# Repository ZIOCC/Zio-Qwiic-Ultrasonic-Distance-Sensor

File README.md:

# Zio Qwiic Ultrasonic Distance Sensor (HC-SR04)

> This product can be available for purchase [here](https://www.smart-prototyping.com/Zio-Ultrasonic-Distance-Sensor.html).

#### Description

This is a [Qwiic](https://www.smart-prototyping.com/Qwiic.html) I2C version of ultrasonic sensor in our Qwiic family. TOF sensor is great, precise and fast, but this Ultrasonic sensor can provide wider detecting angle than TOF sensor and longer distance (3-400cm).

With this module we used a STM8 MCU as gateway to deal with sensor’s digital data in MCU, and send it out via I2C. So you don’t need to care about how it works inside the STM8, just trade it as an I2C device. In case you are interesting, you can check out the STM8 code at the bottom of the links.

We also break the serial pins just like the normal HC-SR04 module. The pins are not pre-soldered. We use an MCU (ATTINY85-20SU) as gateway to turn it into an I2C device.

For additional information on how the Ultrasonic sensor works, you can check out this [page](http://arduinoinfo.mywikis.net/wiki/UltraSonicDistance)!

Note: Try to avoid touching the pins and pads on the backside, the sensor measurement is based on analog single, touching these pins and pads will make the result unstable. 

#### Specification

* Operating Voltage: 3.3V
* Detecting Angle: 15 degree
* Sensor range: 2cm to 400cm
* Accuracy: 3mm
* MCU on board: STM8L051
* I2C Address: 0x00
* Dimension: 21.5x 45.5mm
* Weight: 9.2g

#### Links

* [Eagle File](https://github.com/ZIOCC/Zio-Qwiic-Ultrasonic-Distance-Sensor/)
* [Example Code](https://github.com/ZIOCC/Zio-Qwiic-Ultrasonic-Distance-Sensor/tree/master/Arduino)

###### About Zio
> Zio is a new line of open sourced, compact, and grid layout boards, fully integrated for Arduino and Qwiic ecosystem. Designed ideally for wearables, robotics, small-space limitations or other on the go projects. Check out other awesome Zio products [here](https://www.smart-prototyping.com/Zio).

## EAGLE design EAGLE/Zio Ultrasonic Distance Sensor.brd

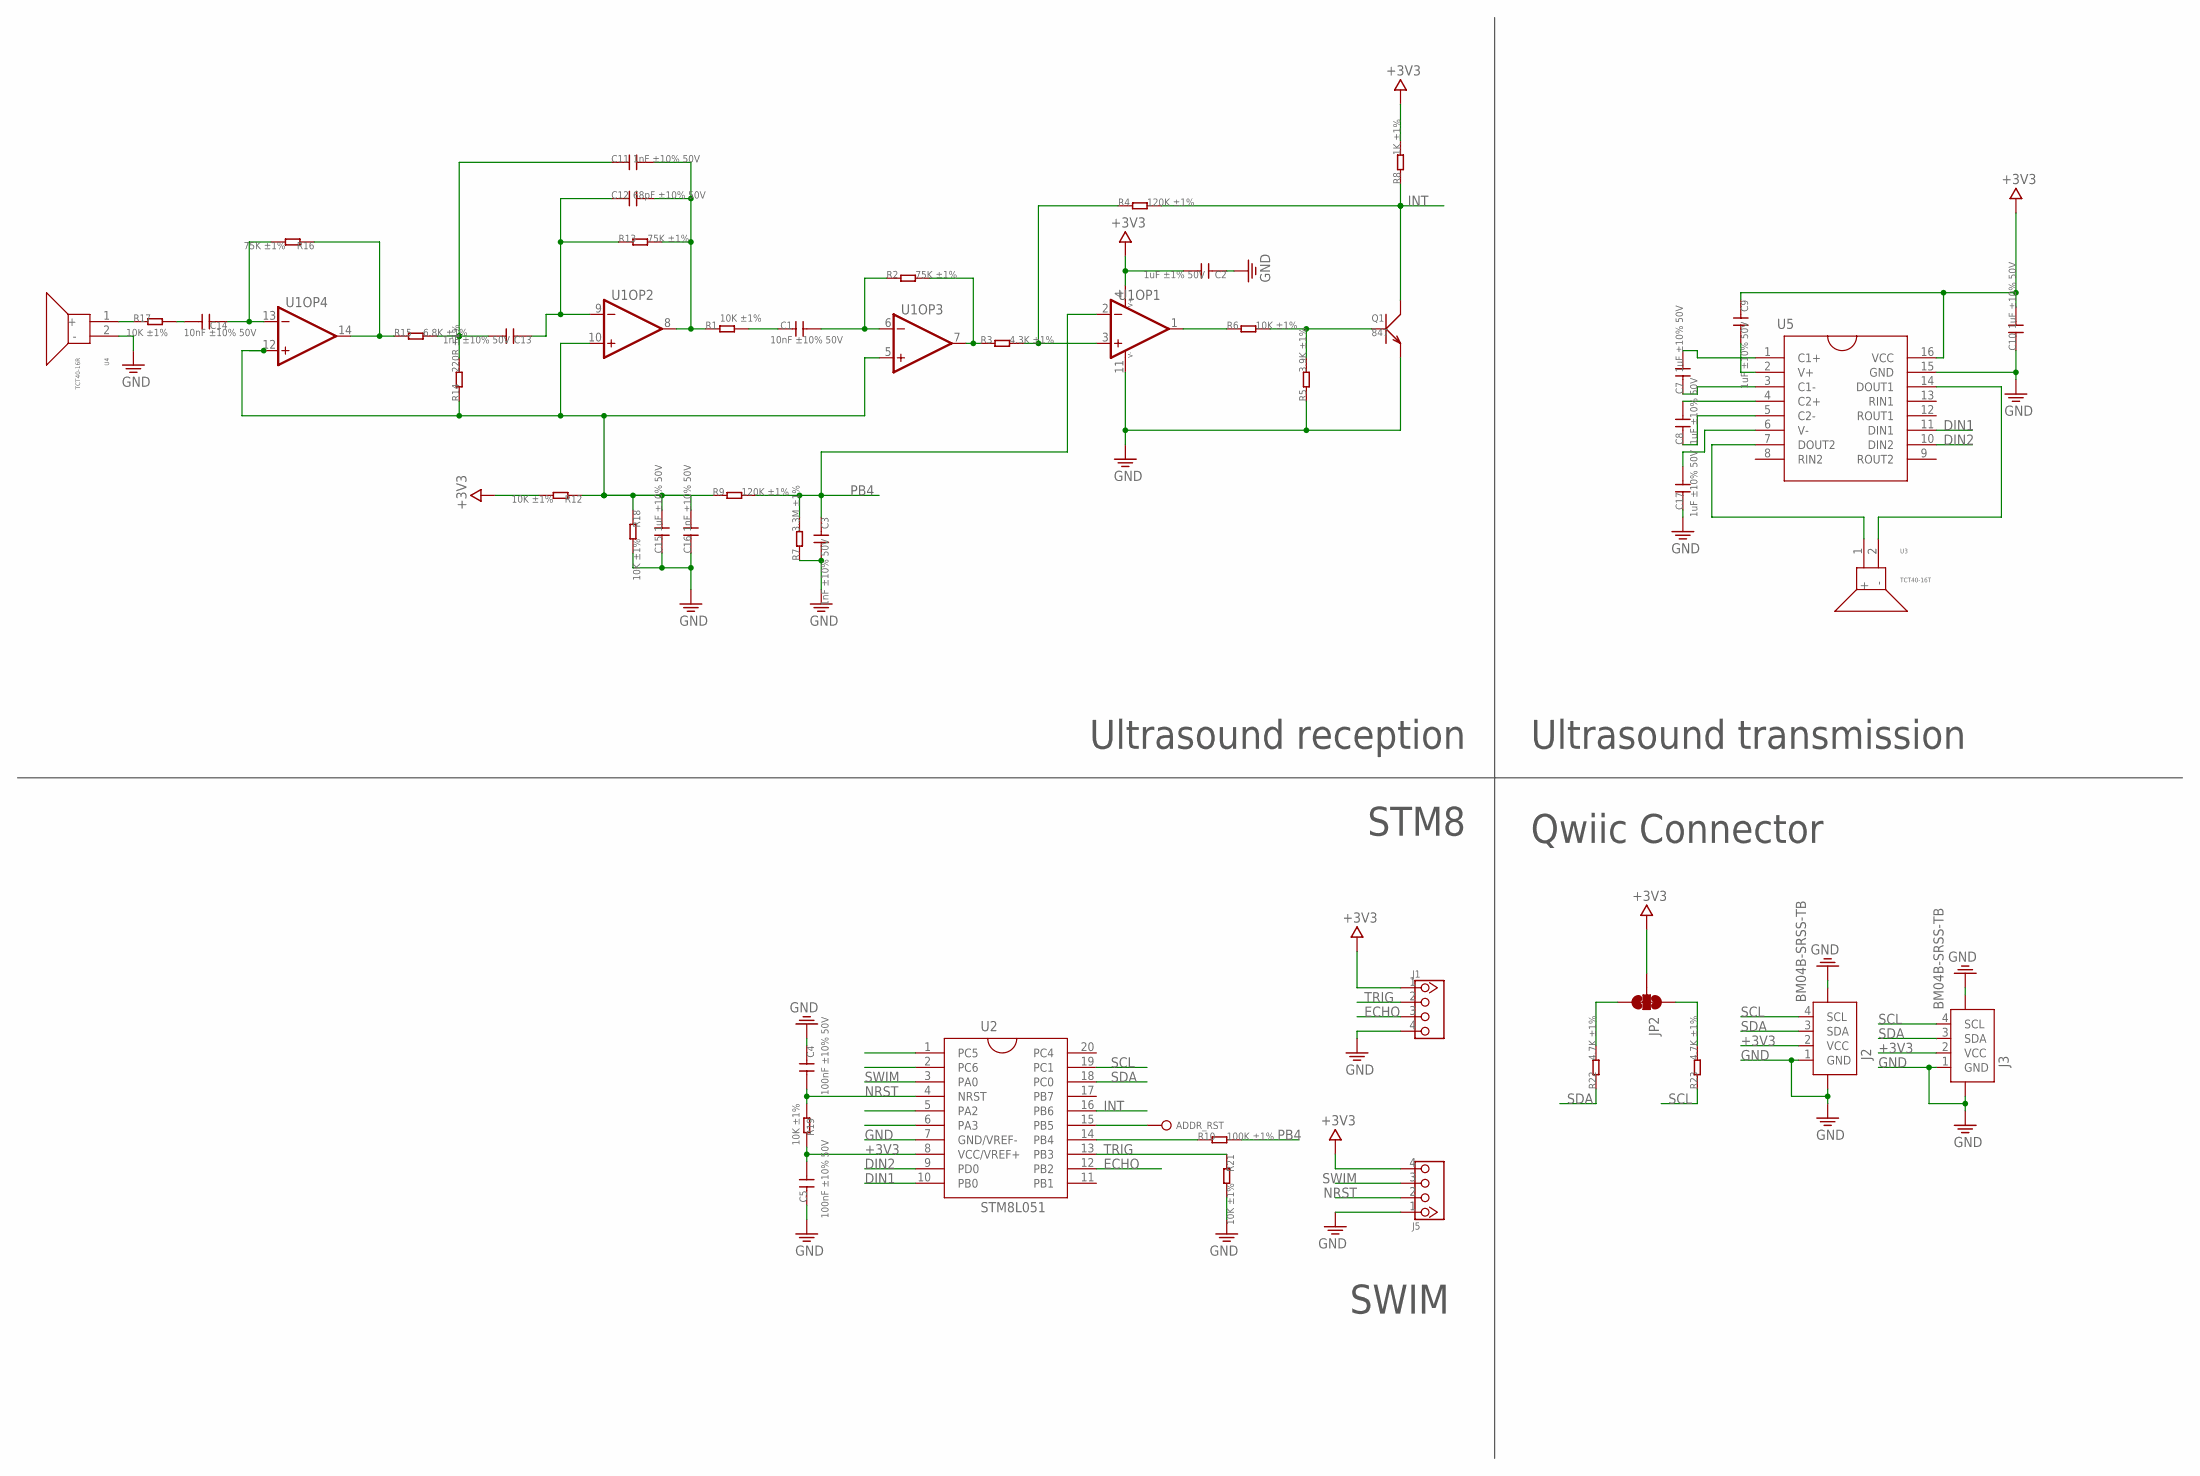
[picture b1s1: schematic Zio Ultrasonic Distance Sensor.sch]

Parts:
ADDR_RST: TEST_POINT35MIL; 1P-35MIL
C1, C14: 10nF ±10% 50V; 0603
C2: 1uF ±1% 50V; 0603
C3, C11, C13, C16: 1nF ±10% 50V; 0603
C4, C5: 100nF ±10% 50V; 0603
C7, C8, C9, C10, C15, C17: 1uF ±10% 50V; 0603
C12: 68pF ±10% 50V; 0603
J1: HEADER-4P-60/35MIL; 4P-65/35MIL
J2, J3: BM04B-SRSS-TB; JST-SH-4P-90
J5: HEADER-4P-TEST_3.08_4P; TEST_3.08_4P
JP2: SMT-JUMPER_3_2-NC_TRACE
Q1: 847; SOT23
R1, R6, R12, R17, R18, R19, R21: 10K ±1%; 0603
R2, R13, R16: 75K ±1%; 0603
R3: 4.3K ±1%; 0603
R4, R9: 120K ±1%; 0603
R5: 3.9K ±1%; 0603
R7: 3.3M ±1%; 0603
R8: 1K ±1%; 0603
R10: 100K ±1%; 0603
R14: 220R ±1%; 0603
R15: 6.8K ±1%; 0603
R22, R23: 4.7K ±1%; 0603
U1: LMV324; SO014
U2: STM8L051; TSSOP20
U3: TCT40-16T; TCT40-16T/R
U4: TCT40-16R; TCT40-16T/R
U5: UT3232G-S16-RSOIC-16; SOIC16

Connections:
+3V3: C2.2, C5.1, C9.1, C10.2, J1.1, J2.2 (VCC), J3.2 (VCC), J5.4, JP2.2, R8.2, R12.2, R19.2, U1.4 (V+), U2.8 (VCC/VREF+), U5.16 (VCC)
DIN1: U2.10 (PB0), U5.11 (DIN1)
DIN2: U2.9 (PD0), U5.10 (DIN2)
ECHO: J1.3, U2.12 (PB2)
GND: C2.1, C3.2, C4.1, C5.2, C10.1, C15.1, C16.1, C17.1, J1.4, J2.1 (GND), J2.5, J2.6, J3.1 (GND), J3.5, J3.6, J5.1, Q1.2 (E), R5.1, R7.1, R18.2, R21.2, U1.11 (V-), U2.7 (GND/VREF-), U4.2 (-), U5.15 (GND)
INT: Q1.3 (C), R4.2, R8.1, U2.16 (PB6)
unnamed: R2.2, R3.1, U1.7 (OUT)
unnamed: C1.1, R2.1, U1.6 (IN-)
unnamed: C1.2, R1.2
unnamed: R3.2, R4.1, U1.3 (IN+)
unnamed: Q1.1 (B), R5.2, R6.2
unnamed: R6.1, U1.1 (OUT)
unnamed: C7.2, U5.1 (C1+)
unnamed: C12.1, C13.1, R13.1, U1.9 (IN-)
unnamed: C11.2, C12.2, R1.1, R13.2, U1.8 (OUT)
unnamed: C15.2, C16.2, R9.1, R12.1, R14.1, R18.1, U1.5 (IN+), U1.10 (IN+), U1.12 (IN+)
unnamed: C11.1, C13.2, R14.2, R15.2
unnamed: C7.1, U5.3 (C1-)
unnamed: R15.1, R16.1, U1.14 (OUT)
unnamed: C14.1, R16.2, U1.13 (IN-)
unnamed: C14.2, R17.2
unnamed: C8.2, U5.4 (C2+)
unnamed: C8.1, U5.5 (C2-)
unnamed: JP2.3, R22.2
unnamed: JP2.1, R23.2
unnamed: C9.2, U5.2 (V+)
unnamed: C17.2, U5.6 (V-)
unnamed: U3.2 (-), U5.14 (DOUT1)
unnamed: U3.1 (+), U5.7 (DOUT2)
unnamed: R17.1, U4.1 (+)
unnamed: ADDR_RST.P$1, U2.15 (PB5)
unnamed: R10.1, U2.14 (PB4)
NRST: C4.2, J5.2, R19.1, U2.4 (NRST)
PB4: C3.1, R7.2, R9.2, R10.2, U1.2 (IN-)
SCL: J2.4 (SCL), J3.4 (SCL), R23.1, U2.19 (PC1)
SDA: J2.3 (SDA), J3.3 (SDA), R22.1, U2.18 (PC0)
SWIM: J5.3, U2.3 (PA0)
TRIG: J1.2, R21.1, U2.13 (PB3)

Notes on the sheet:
SWIM
Qwiic Connector
Ultrasound transmission
Ultrasound reception
STM8

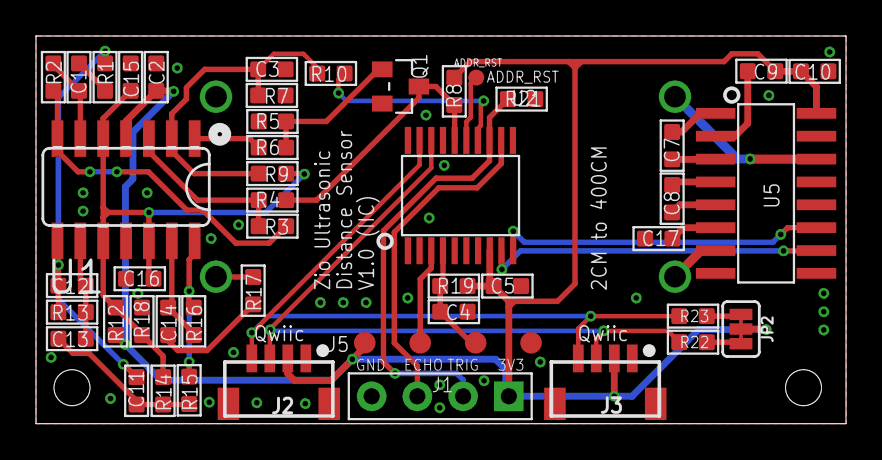
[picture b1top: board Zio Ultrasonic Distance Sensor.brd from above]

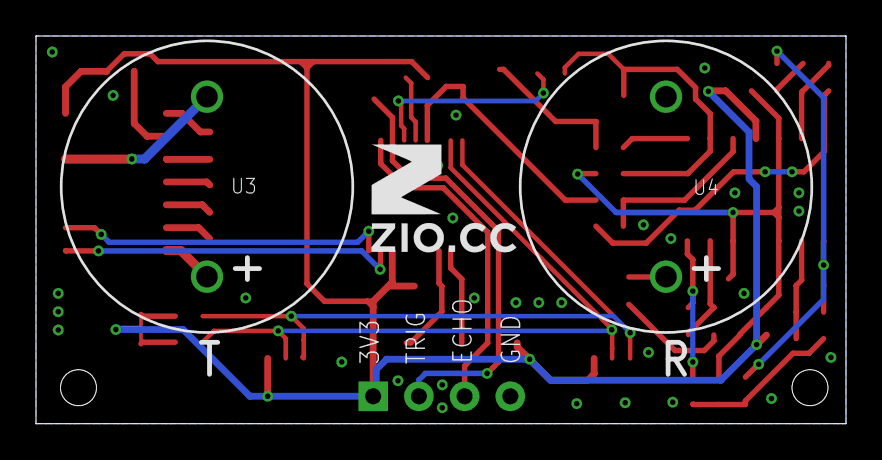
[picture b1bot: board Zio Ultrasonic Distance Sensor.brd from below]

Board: 2 copper layers, 45.0 x 21.5 mm, 50 parts (3 on the bottom side), 38 nets.

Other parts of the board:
U$5: 6MM

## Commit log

2023-07-17 Create Isaac
